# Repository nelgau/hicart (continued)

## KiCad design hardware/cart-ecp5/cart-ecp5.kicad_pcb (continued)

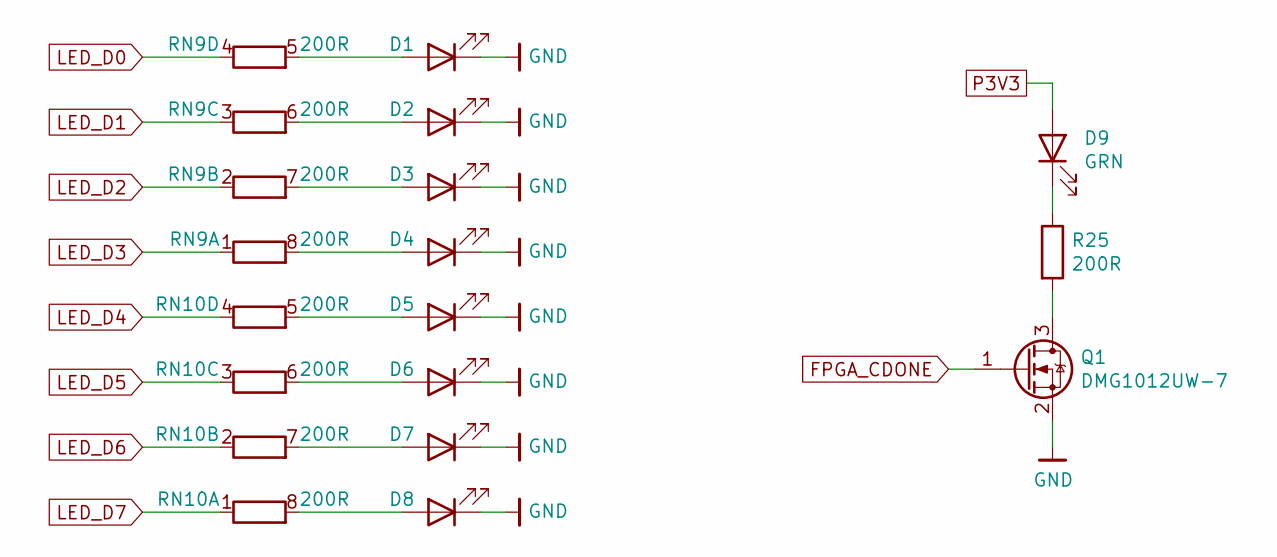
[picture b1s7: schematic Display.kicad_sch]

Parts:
D1, D2, D3, D4, D5, D6, D7, D8, D9: GRN; D_0603_1608Metric; MPN LTST-C191KGKT
Q1: DMG1012UW-7; SOT-323_SC-70; MPN DMG1012UW-7
R25: 200R; R_0402_1005Metric; MPN RC0402JR-07200RL
RN9, RN10: 200R; R_Array_Convex_4x0603; MPN YC164-JR-07200RL

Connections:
FPGA_CDONE: Q1.1 (G); also elsewhere on the board
GND: D1.1 (K), D2.1 (K), D3.1 (K), D4.1 (K), D5.1 (K), D6.1 (K), D7.1 (K), D8.1 (K), Q1.2 (S); also elsewhere on the board
LED_D0: RN9.4 (R4.1); also elsewhere on the board
LED_D1: RN9.3 (R3.1); also elsewhere on the board
LED_D2: RN9.2 (R2.1); also elsewhere on the board
LED_D3: RN9.1 (R1.1); also elsewhere on the board
LED_D4: RN10.4 (R4.1); also elsewhere on the board
LED_D5: RN10.3 (R3.1); also elsewhere on the board
LED_D6: RN10.2 (R2.1); also elsewhere on the board
LED_D7: RN10.1 (R1.1); also elsewhere on the board
unnamed: D1.2 (A), RN9.5 (R4.2)
unnamed: D2.2 (A), RN9.6 (R3.2)
unnamed: D3.2 (A), RN9.7 (R2.2)
unnamed: D4.2 (A), RN9.8 (R1.2)
unnamed: D5.2 (A), RN10.5 (R4.2)
unnamed: D6.2 (A), RN10.6 (R3.2)
unnamed: D7.2 (A), RN10.7 (R2.2)
unnamed: D8.2 (A), RN10.8 (R1.2)
unnamed: D9.1 (K), R25.1
unnamed: Q1.3 (D), R25.2
P3V3: D9.2 (A); also elsewhere on the board

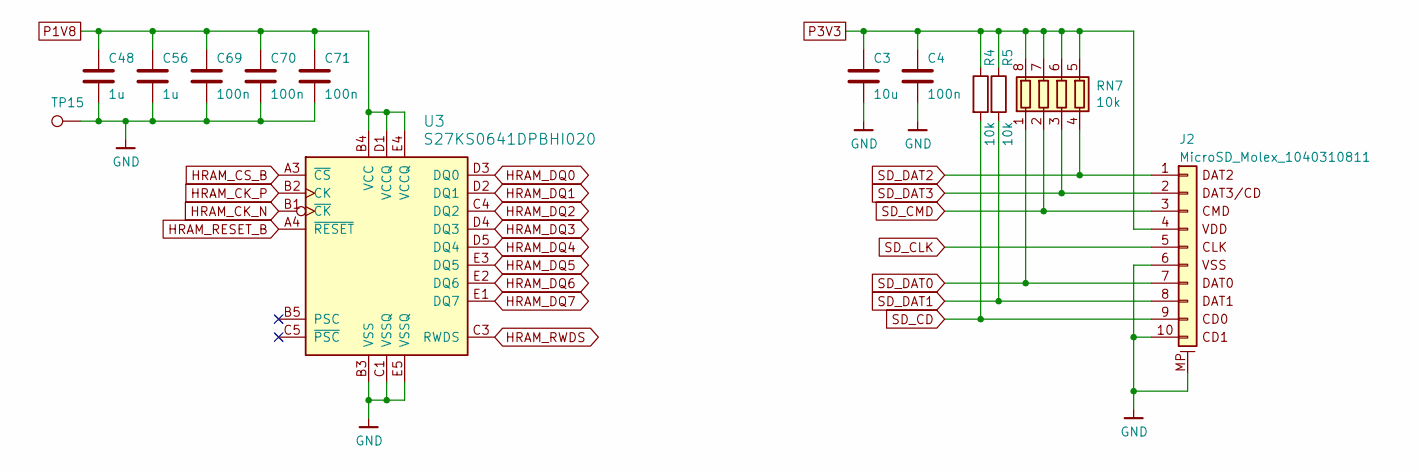
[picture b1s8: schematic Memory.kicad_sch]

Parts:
C3: 10u; C_0603_1608Metric; MPN CL10A106MQ8NNND
C4, C69, C70, C71: 100n; C_0402_1005Metric; MPN CL05B104KO5NNNC
C48, C56: 1u; C_0402_1005Metric; MPN CL05A105KO5NNNC
J2: MicroSD_Molex_1040310811; MPN 104031-0811
R4, R5: 10k; R_0402_1005Metric; MPN RC0402FR-0710KL
RN7: 10k; R_Array_Convex_4x0603; MPN YC164-FR-0710KL
TP15: TestPoint; TestPoint_Pad_D1.0mm
U3: S27KS0641DPBHI020; BGA-24_6.0x8.0mm_Layout5x5_P1.0mm_Pad0.4mm; MPN S27KS0641DPBHI020

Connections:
GND: C3.2, C4.2, C48.2, C56.2, C69.2, C70.2, C71.2, J2.6, J2.10 (DET), J2.MP (MountPin), TP15.1, U3.B3 (VSS), U3.C1 (VSSQ), U3.E5 (VSSQ); also elsewhere on the board
HRAM_CK_N: U3.B1 (~CK); also elsewhere on the board
HRAM_CK_P: U3.B2 (CK); also elsewhere on the board
HRAM_CS_B: U3.A3 (~CS); also elsewhere on the board
HRAM_DQ0: U3.D3 (DQ0); also elsewhere on the board
HRAM_DQ1: U3.D2 (DQ1); also elsewhere on the board
HRAM_DQ2: U3.C4 (DQ2); also elsewhere on the board
HRAM_DQ3: U3.D4 (DQ3); also elsewhere on the board
HRAM_DQ4: U3.D5 (DQ4); also elsewhere on the board
HRAM_DQ5: U3.E3 (DQ5); also elsewhere on the board
HRAM_DQ6: U3.E2 (DQ6); also elsewhere on the board
HRAM_DQ7: U3.E1 (DQ7); also elsewhere on the board
HRAM_RESET_B: U3.A4 (~RESET); also elsewhere on the board
HRAM_RWDS: U3.C3 (RWDS); also elsewhere on the board
P1V8: C48.1, C56.1, C69.1, C70.1, C71.1, U3.B4 (VCC), U3.D1 (VCCQ), U3.E4 (VCCQ); also elsewhere on the board
P3V3: C3.1, C4.1, J2.4, R4.1, R5.1, RN7.5 (R4.2), RN7.6 (R3.2), RN7.7 (R2.2), RN7.8 (R1.2); also elsewhere on the board
SD_CD: J2.9, R4.2; also elsewhere on the board
SD_CLK: J2.5; also elsewhere on the board
SD_CMD: J2.3, RN7.2 (R2.1); also elsewhere on the board
SD_DAT0: J2.7, RN7.1 (R1.1); also elsewhere on the board
SD_DAT1: J2.8, R5.2; also elsewhere on the board
SD_DAT2: J2.1, RN7.4 (R4.1); also elsewhere on the board
SD_DAT3: J2.2, RN7.3 (R3.1); also elsewhere on the board

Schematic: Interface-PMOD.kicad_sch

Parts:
J6: Conn_02x06_Odd_Even; PinSocket_2x06_P2.54mm_Horizontal

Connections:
GND: J6.3, J6.4; also elsewhere on the board
P3V3: J6.1, J6.2; also elsewhere on the board
PMOD_P1_D0: J6.11; also elsewhere on the board
PMOD_P1_D1: J6.9; also elsewhere on the board
PMOD_P1_D2: J6.7; also elsewhere on the board
PMOD_P1_D3: J6.5; also elsewhere on the board
PMOD_P1_D4: J6.12; also elsewhere on the board
PMOD_P1_D5: J6.10; also elsewhere on the board
PMOD_P1_D6: J6.8; also elsewhere on the board
PMOD_P1_D7: J6.6; also elsewhere on the board

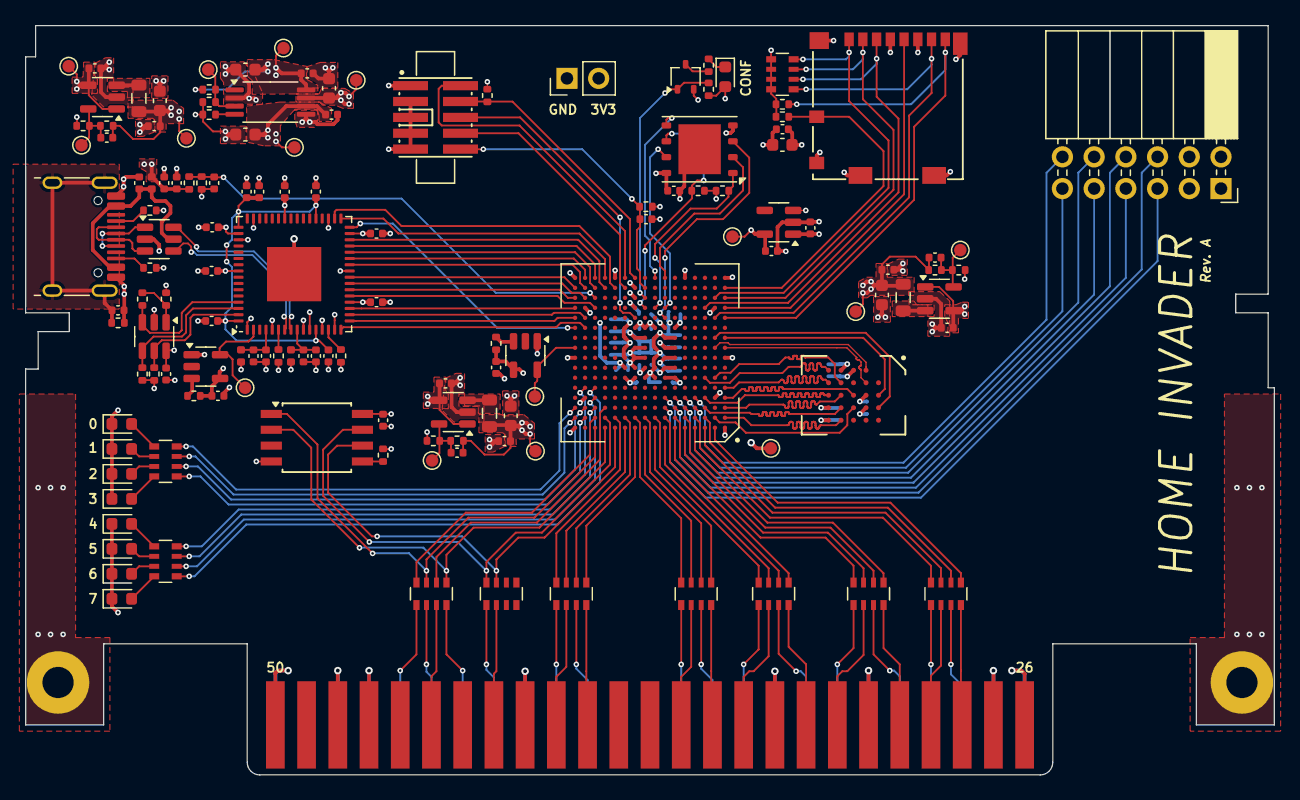
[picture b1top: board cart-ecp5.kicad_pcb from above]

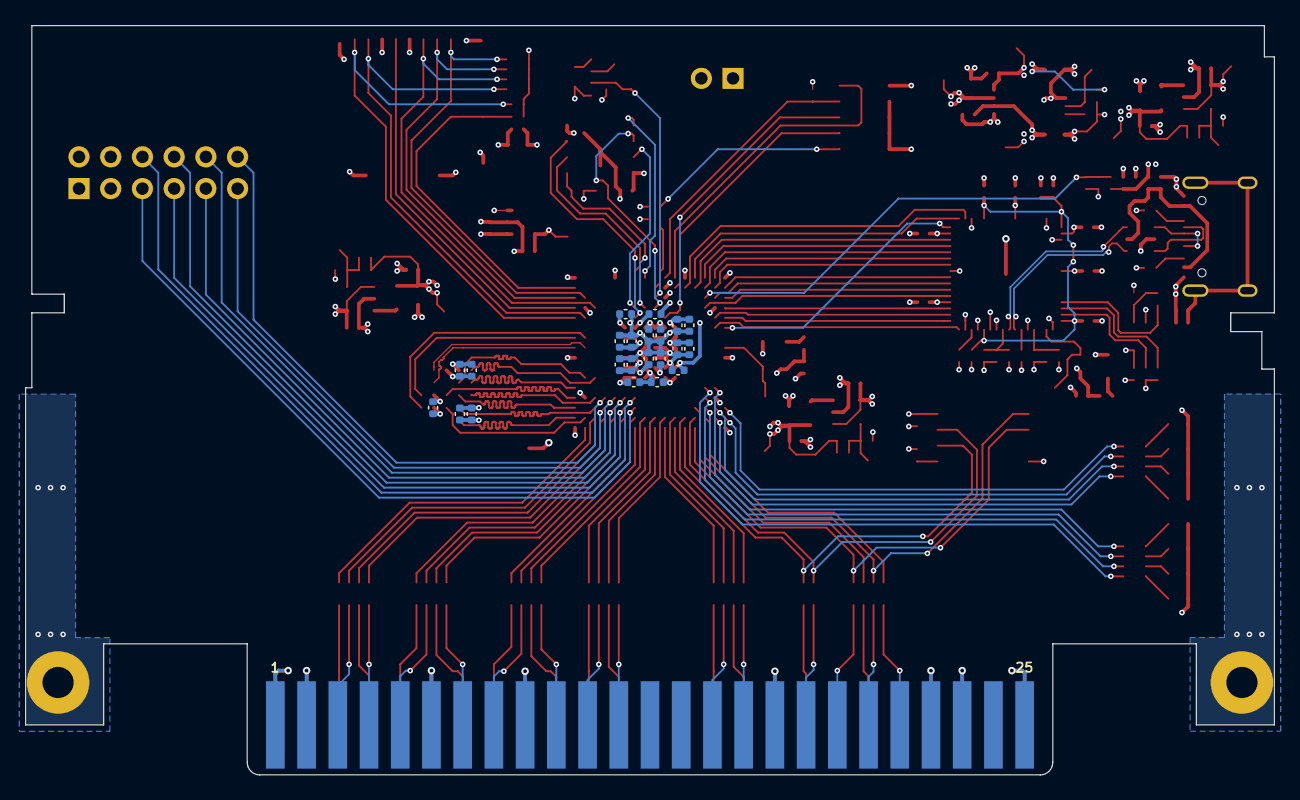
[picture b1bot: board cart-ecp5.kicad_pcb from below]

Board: 4 copper layers, 100.0 x 60.0 mm, 160 parts (22 on the bottom side), 165 nets.

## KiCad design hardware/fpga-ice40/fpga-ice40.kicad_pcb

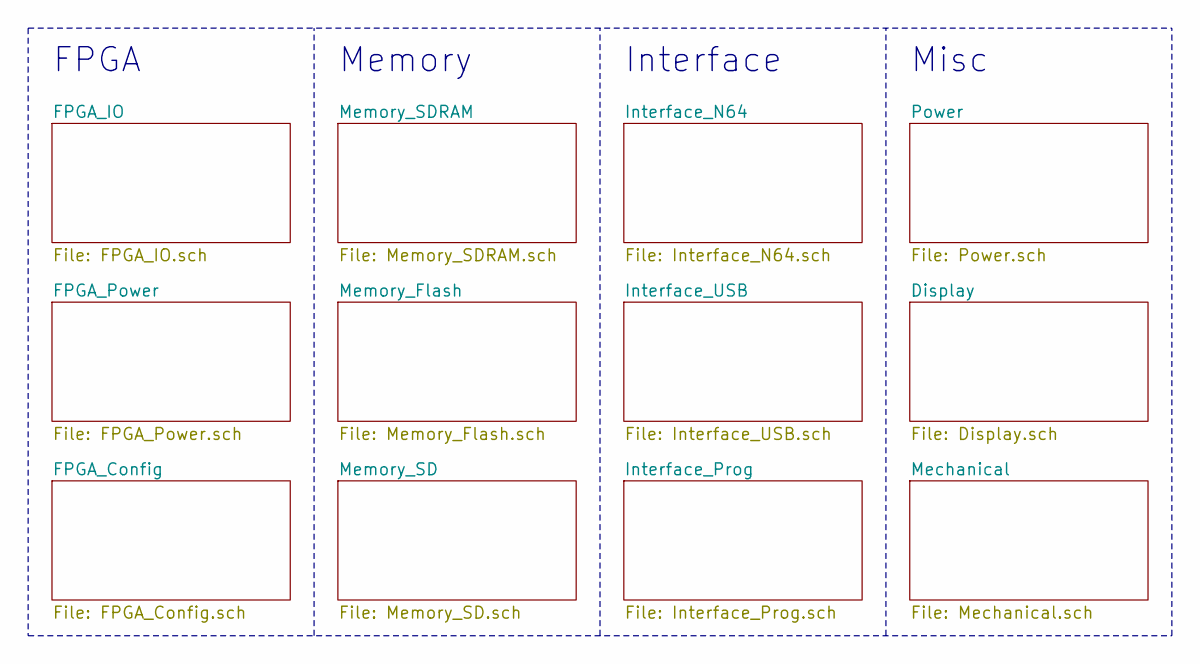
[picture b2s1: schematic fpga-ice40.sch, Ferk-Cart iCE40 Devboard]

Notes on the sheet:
Memory
Interface
Misc
FPGA

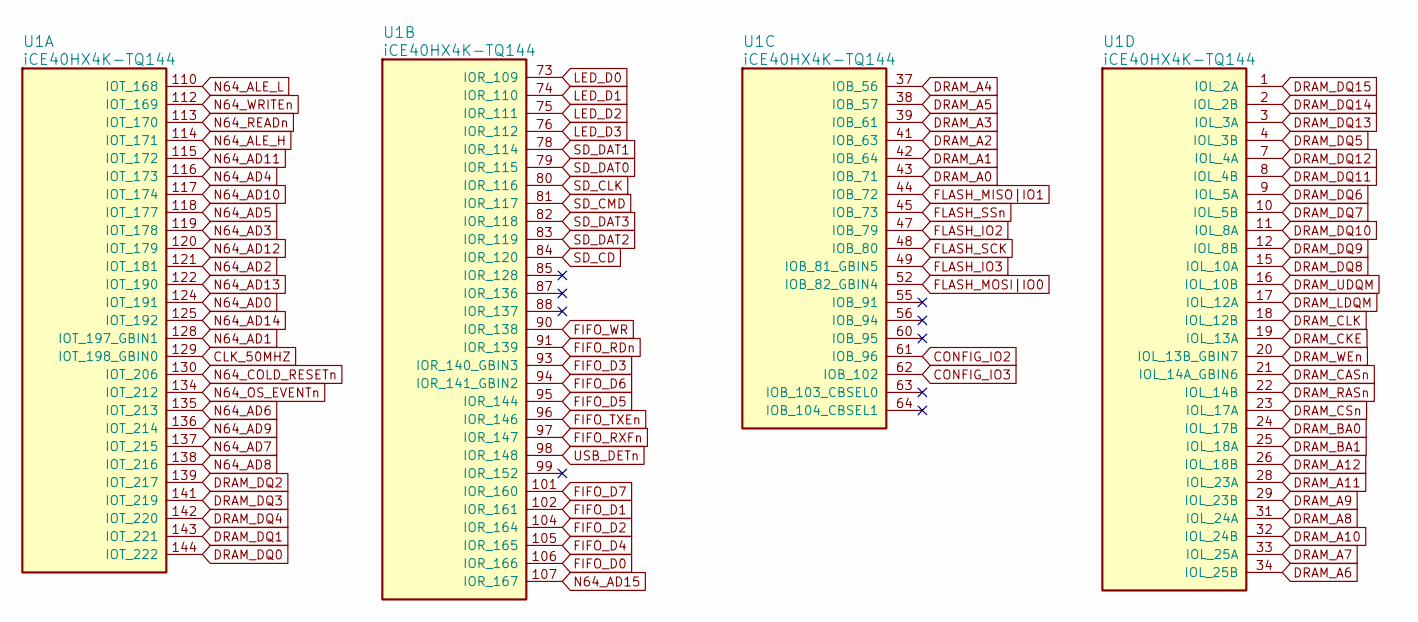
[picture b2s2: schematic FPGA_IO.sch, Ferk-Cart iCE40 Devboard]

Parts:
U1: iCE40HX4K-TQ144; TQFP-144_20x20mm_P0.5mm; MPN iCE40HX4K-TQ144

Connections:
CLK_50MHZ: U1.129 (IOT_198_GBIN0); also elsewhere on the board
CONFIG_IO2: U1.61 (IOB_96); also elsewhere on the board
CONFIG_IO3: U1.62 (IOB_102); also elsewhere on the board
DRAM_A0: U1.43 (IOB_71); also elsewhere on the board
DRAM_A1: U1.42 (IOB_64); also elsewhere on the board
DRAM_A2: U1.41 (IOB_63); also elsewhere on the board
DRAM_A3: U1.39 (IOB_61); also elsewhere on the board
DRAM_A4: U1.37 (IOB_56); also elsewhere on the board
DRAM_A5: U1.38 (IOB_57); also elsewhere on the board
DRAM_A6: U1.34 (IOL_25B); also elsewhere on the board
DRAM_A7: U1.33 (IOL_25A); also elsewhere on the board
DRAM_A8: U1.31 (IOL_24A); also elsewhere on the board
DRAM_A9: U1.29 (IOL_23B); also elsewhere on the board
DRAM_A10: U1.32 (IOL_24B); also elsewhere on the board
DRAM_A11: U1.28 (IOL_23A); also elsewhere on the board
DRAM_A12: U1.26 (IOL_18B); also elsewhere on the board
DRAM_BA0: U1.24 (IOL_17B); also elsewhere on the board
DRAM_BA1: U1.25 (IOL_18A); also elsewhere on the board
DRAM_CASn: U1.21 (IOL_14A_GBIN6); also elsewhere on the board
DRAM_CKE: U1.19 (IOL_13A); also elsewhere on the board
DRAM_CLK: U1.18 (IOL_12B); also elsewhere on the board
DRAM_CSn: U1.23 (IOL_17A); also elsewhere on the board
DRAM_DQ0: U1.144 (IOT_222); also elsewhere on the board
DRAM_DQ1: U1.143 (IOT_221); also elsewhere on the board
DRAM_DQ2: U1.139 (IOT_217); also elsewhere on the board
DRAM_DQ3: U1.141 (IOT_219); also elsewhere on the board
DRAM_DQ4: U1.142 (IOT_220); also elsewhere on the board
DRAM_DQ5: U1.4 (IOL_3B); also elsewhere on the board
DRAM_DQ6: U1.9 (IOL_5A); also elsewhere on the board
DRAM_DQ7: U1.10 (IOL_5B); also elsewhere on the board
DRAM_DQ8: U1.15 (IOL_10A); also elsewhere on the board
DRAM_DQ9: U1.12 (IOL_8B); also elsewhere on the board
DRAM_DQ10: U1.11 (IOL_8A); also elsewhere on the board
DRAM_DQ11: U1.8 (IOL_4B); also elsewhere on the board
DRAM_DQ12: U1.7 (IOL_4A); also elsewhere on the board
DRAM_DQ13: U1.3 (IOL_3A); also elsewhere on the board
DRAM_DQ14: U1.2 (IOL_2B); also elsewhere on the board
DRAM_DQ15: U1.1 (IOL_2A); also elsewhere on the board
DRAM_LDQM: U1.17 (IOL_12A); also elsewhere on the board
DRAM_RASn: U1.22 (IOL_14B); also elsewhere on the board
DRAM_UDQM: U1.16 (IOL_10B); also elsewhere on the board
DRAM_WEn: U1.20 (IOL_13B_GBIN7); also elsewhere on the board
FIFO_D0: U1.106 (IOR_166); also elsewhere on the board
FIFO_D1: U1.102 (IOR_161); also elsewhere on the board
FIFO_D2: U1.104 (IOR_164); also elsewhere on the board
FIFO_D3: U1.93 (IOR_140_GBIN3); also elsewhere on the board
FIFO_D4: U1.105 (IOR_165); also elsewhere on the board
FIFO_D5: U1.95 (IOR_144); also elsewhere on the board
FIFO_D6: U1.94 (IOR_141_GBIN2); also elsewhere on the board
FIFO_D7: U1.101 (IOR_160); also elsewhere on the board
FIFO_RDn: U1.91 (IOR_139); also elsewhere on the board
FIFO_RXFn: U1.97 (IOR_147); also elsewhere on the board
FIFO_TXEn: U1.96 (IOR_146); also elsewhere on the board
FIFO_WR: U1.90 (IOR_138); also elsewhere on the board
FLASH_IO2: U1.47 (IOB_79); also elsewhere on the board
FLASH_IO3: U1.49 (IOB_81_GBIN5); also elsewhere on the board
FLASH_MISO|IO1: U1.44 (IOB_72); also elsewhere on the board
FLASH_MOSI|IO0: U1.52 (IOB_82_GBIN4); also elsewhere on the board
FLASH_SCK: U1.48 (IOB_80); also elsewhere on the board
FLASH_SSn: U1.45 (IOB_73); also elsewhere on the board
LED_D0: U1.73 (IOR_109); also elsewhere on the board
LED_D1: U1.74 (IOR_110); also elsewhere on the board
LED_D2: U1.75 (IOR_111); also elsewhere on the board
LED_D3: U1.76 (IOR_112); also elsewhere on the board
N64_AD0: U1.124 (IOT_191); also elsewhere on the board
N64_AD1: U1.128 (IOT_197_GBIN1); also elsewhere on the board
N64_AD2: U1.121 (IOT_181); also elsewhere on the board
N64_AD3: U1.119 (IOT_178); also elsewhere on the board
N64_AD4: U1.116 (IOT_173); also elsewhere on the board
N64_AD5: U1.118 (IOT_177); also elsewhere on the board
N64_AD6: U1.135 (IOT_213); also elsewhere on the board
N64_AD7: U1.137 (IOT_215); also elsewhere on the board
N64_AD8: U1.138 (IOT_216); also elsewhere on the board
N64_AD9: U1.136 (IOT_214); also elsewhere on the board
N64_AD10: U1.117 (IOT_174); also elsewhere on the board
N64_AD11: U1.115 (IOT_172); also elsewhere on the board
N64_AD12: U1.120 (IOT_179); also elsewhere on the board
N64_AD13: U1.122 (IOT_190); also elsewhere on the board
N64_AD14: U1.125 (IOT_192); also elsewhere on the board
N64_AD15: U1.107 (IOR_167); also elsewhere on the board
N64_ALE_H: U1.114 (IOT_171); also elsewhere on the board
N64_ALE_L: U1.110 (IOT_168); also elsewhere on the board
N64_COLD_RESETn: U1.130 (IOT_206); also elsewhere on the board
N64_OS_EVENTn: U1.134 (IOT_212); also elsewhere on the board
N64_READn: U1.113 (IOT_170); also elsewhere on the board
N64_WRITEn: U1.112 (IOT_169); also elsewhere on the board
SD_CD: U1.84 (IOR_120); also elsewhere on the board
SD_CLK: U1.80 (IOR_116); also elsewhere on the board
SD_CMD: U1.81 (IOR_117); also elsewhere on the board
SD_DAT0: U1.79 (IOR_115); also elsewhere on the board
SD_DAT1: U1.78 (IOR_114); also elsewhere on the board
SD_DAT2: U1.83 (IOR_119); also elsewhere on the board
SD_DAT3: U1.82 (IOR_118); also elsewhere on the board
USB_DETn: U1.98 (IOR_148); also elsewhere on the board

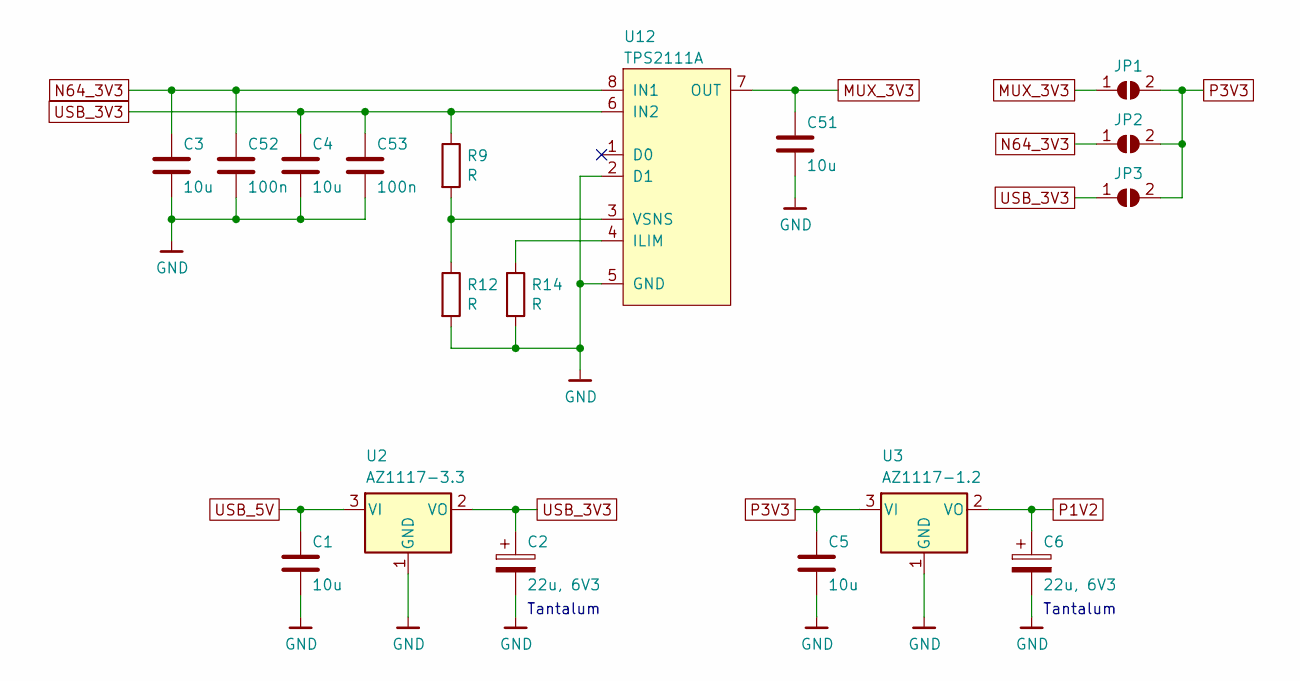
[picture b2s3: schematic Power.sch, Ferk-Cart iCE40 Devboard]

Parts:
C1, C5: 10u; C_0805_2012Metric; MPN CL21A106KAYNNNE
C2, C6: 22u, 6V3; CP_EIA-2012-15_AVX-P; MPN TAJP226M006RNJ
C3, C4, C51: 10u; C_0805_2012Metric
C52, C53: 100n; C_0603_1608Metric
JP1, JP2, JP3: SolderJumper_2_Open; SolderJumper-2_P1.3mm_Open_TrianglePad1.0x1.5mm
R9, R12, R14: R; R_0603_1608Metric
U2: AZ1117-3.3; SOT-223-3_TabPin2; MPN AZ1117H-3.3TRE1
U3: AZ1117-1.2; SOT-223-3_TabPin2; MPN AZ1117H-1.2TRE1
U12: TPS2111A; TSSOP-8_4.4x3mm_P0.65mm

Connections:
GND: C1.2, C2.2, C3.2, C4.2, C5.2, C6.2, C51.2, C52.2, C53.2, R12.2, R14.2, U2.1 (GND), U3.1 (GND), U12.2 (D1), U12.5 (GND); also elsewhere on the board
MUX_3V3: C51.1, JP1.1 (A), U12.7 (OUT)
N64_3V3: C3.1, C52.1, JP2.1 (A), U12.8 (IN1); also elsewhere on the board
unnamed: R9.2, R12.1, U12.3 (VSNS)
unnamed: R14.1, U12.4 (ILIM)
P1V2: C6.1, U3.2 (VO); also elsewhere on the board
P3V3: C5.1, JP1.2 (B), JP2.2 (B), JP3.2 (B), U3.3 (VI); also elsewhere on the board
USB_3V3: C2.1, C4.1, C53.1, JP3.1 (A), R9.1, U2.2 (VO), U12.6 (IN2)
USB_5V: C1.1, U2.3 (VI); also elsewhere on the board

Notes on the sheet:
Tantalum

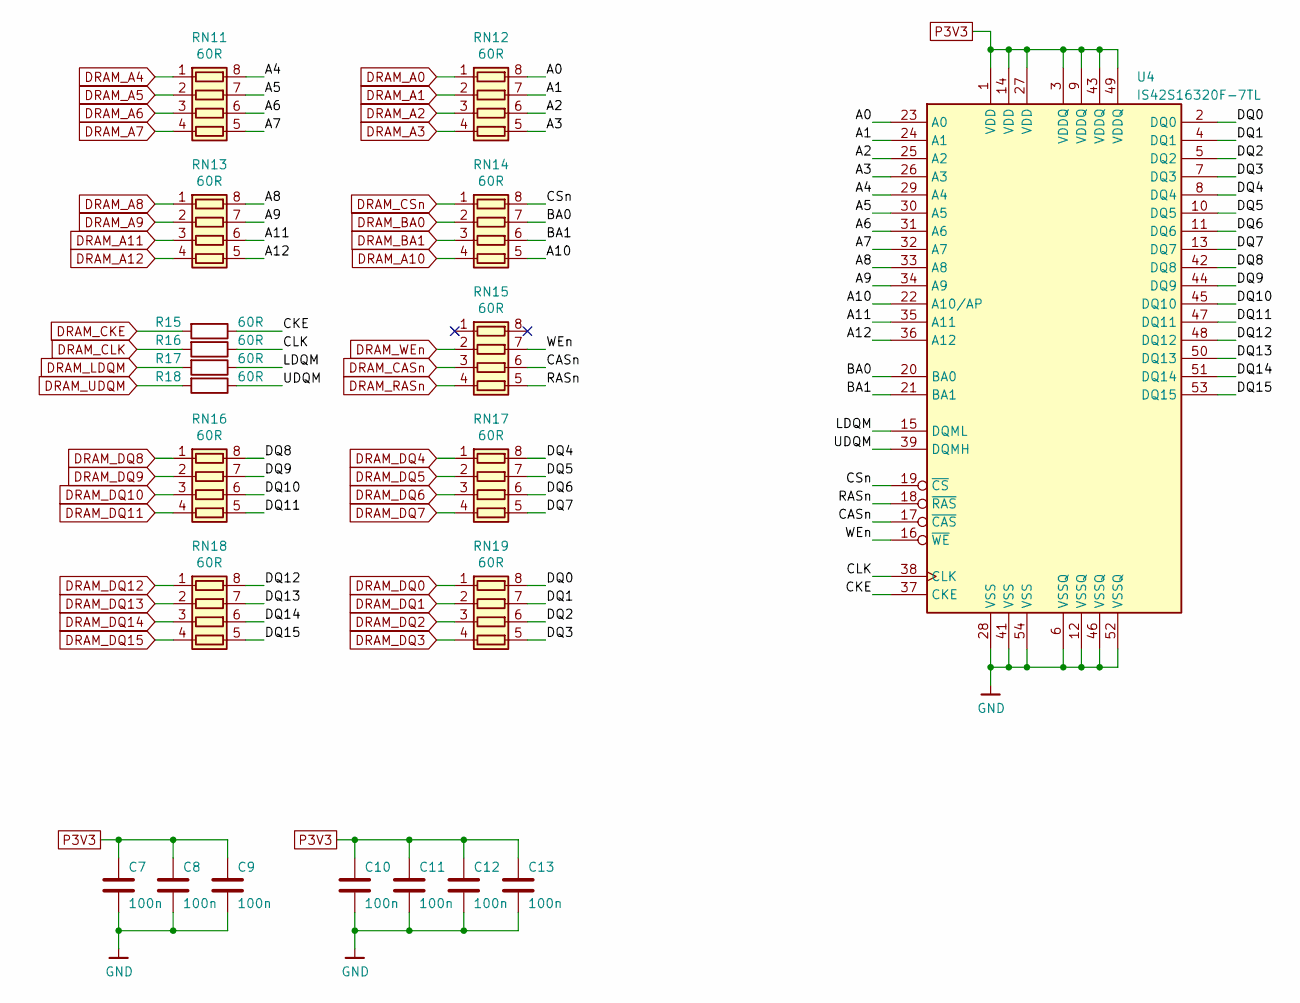
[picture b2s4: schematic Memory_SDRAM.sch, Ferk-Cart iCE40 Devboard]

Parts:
C7, C8, C9, C10, C11, C12, C13: 100n; C_0603_1608Metric; MPN CL10B104KB8NNNC
R15, R16, R17, R18: 60R; R_0603_1608Metric
RN11, RN12, RN13, RN14, RN15, RN16, RN17, RN18, RN19: 60R; R_Array_Convex_4x0603
U4: IS42S16320F-7TL; TSOP-II-54_22.2x10.16mm_P0.8mm; MPN IS42S16320F-7TL

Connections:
/Memory_SDRAM/A0: RN12.8 (R1.2), U4.23 (A0)
/Memory_SDRAM/A1: RN12.7 (R2.2), U4.24 (A1)
/Memory_SDRAM/A2: RN12.6 (R3.2), U4.25 (A2)
/Memory_SDRAM/A3: RN12.5 (R4.2), U4.26 (A3)
/Memory_SDRAM/A4: RN11.8 (R1.2), U4.29 (A4)
/Memory_SDRAM/A5: RN11.7 (R2.2), U4.30 (A5)
/Memory_SDRAM/A6: RN11.6 (R3.2), U4.31 (A6)
/Memory_SDRAM/A7: RN11.5 (R4.2), U4.32 (A7)
/Memory_SDRAM/A8: RN13.8 (R1.2), U4.33 (A8)
/Memory_SDRAM/A9: RN13.7 (R2.2), U4.34 (A9)
/Memory_SDRAM/A10: RN14.5 (R4.2), U4.22 (A10/AP)
/Memory_SDRAM/A11: RN13.6 (R3.2), U4.35 (A11)
/Memory_SDRAM/A12: RN13.5 (R4.2), U4.36 (A12)
/Memory_SDRAM/BA0: RN14.7 (R2.2), U4.20 (BA0)
/Memory_SDRAM/BA1: RN14.6 (R3.2), U4.21 (BA1)
/Memory_SDRAM/CASn: RN15.6 (R3.2), U4.17 (~CAS)
/Memory_SDRAM/CKE: R15.1, U4.37 (CKE)
/Memory_SDRAM/CLK: R16.1, U4.38 (CLK)
/Memory_SDRAM/CSn: RN14.8 (R1.2), U4.19 (~CS)
/Memory_SDRAM/DQ0: RN19.8 (R1.2), U4.2 (DQ0)
/Memory_SDRAM/DQ1: RN19.7 (R2.2), U4.4 (DQ1)
/Memory_SDRAM/DQ2: RN19.6 (R3.2), U4.5 (DQ2)
/Memory_SDRAM/DQ3: RN19.5 (R4.2), U4.7 (DQ3)
/Memory_SDRAM/DQ4: RN17.8 (R1.2), U4.8 (DQ4)
/Memory_SDRAM/DQ5: RN17.7 (R2.2), U4.10 (DQ5)
/Memory_SDRAM/DQ6: RN17.6 (R3.2), U4.11 (DQ6)
/Memory_SDRAM/DQ7: RN17.5 (R4.2), U4.13 (DQ7)
/Memory_SDRAM/DQ8: RN16.8 (R1.2), U4.42 (DQ8)
/Memory_SDRAM/DQ9: RN16.7 (R2.2), U4.44 (DQ9)
/Memory_SDRAM/DQ10: RN16.6 (R3.2), U4.45 (DQ10)
/Memory_SDRAM/DQ11: RN16.5 (R4.2), U4.47 (DQ11)
/Memory_SDRAM/DQ12: RN18.8 (R1.2), U4.48 (DQ12)
/Memory_SDRAM/DQ13: RN18.7 (R2.2), U4.50 (DQ13)
/Memory_SDRAM/DQ14: RN18.6 (R3.2), U4.51 (DQ14)
/Memory_SDRAM/DQ15: RN18.5 (R4.2), U4.53 (DQ15)
/Memory_SDRAM/LDQM: R17.1, U4.15 (DQML)
/Memory_SDRAM/RASn: RN15.5 (R4.2), U4.18 (~RAS)
/Memory_SDRAM/UDQM: R18.1, U4.39 (DQMH)
/Memory_SDRAM/WEn: RN15.7 (R2.2), U4.16 (~WE)
DRAM_A0: RN12.1 (R1.1); also elsewhere on the board
DRAM_A1: RN12.2 (R2.1); also elsewhere on the board
DRAM_A2: RN12.3 (R3.1); also elsewhere on the board
DRAM_A3: RN12.4 (R4.1); also elsewhere on the board
DRAM_A4: RN11.1 (R1.1); also elsewhere on the board
DRAM_A5: RN11.2 (R2.1); also elsewhere on the board
DRAM_A6: RN11.3 (R3.1); also elsewhere on the board
DRAM_A7: RN11.4 (R4.1); also elsewhere on the board
DRAM_A8: RN13.1 (R1.1); also elsewhere on the board
DRAM_A9: RN13.2 (R2.1); also elsewhere on the board
DRAM_A10: RN14.4 (R4.1); also elsewhere on the board
DRAM_A11: RN13.3 (R3.1); also elsewhere on the board
DRAM_A12: RN13.4 (R4.1); also elsewhere on the board
DRAM_BA0: RN14.2 (R2.1); also elsewhere on the board
DRAM_BA1: RN14.3 (R3.1); also elsewhere on the board
DRAM_CASn: RN15.3 (R3.1); also elsewhere on the board
DRAM_CKE: R15.2; also elsewhere on the board
DRAM_CLK: R16.2; also elsewhere on the board
DRAM_CSn: RN14.1 (R1.1); also elsewhere on the board
DRAM_DQ0: RN19.1 (R1.1); also elsewhere on the board
DRAM_DQ1: RN19.2 (R2.1); also elsewhere on the board
DRAM_DQ2: RN19.3 (R3.1); also elsewhere on the board
DRAM_DQ3: RN19.4 (R4.1); also elsewhere on the board
DRAM_DQ4: RN17.1 (R1.1); also elsewhere on the board
DRAM_DQ5: RN17.2 (R2.1); also elsewhere on the board
DRAM_DQ6: RN17.3 (R3.1); also elsewhere on the board
DRAM_DQ7: RN17.4 (R4.1); also elsewhere on the board
DRAM_DQ8: RN16.1 (R1.1); also elsewhere on the board
DRAM_DQ9: RN16.2 (R2.1); also elsewhere on the board
DRAM_DQ10: RN16.3 (R3.1); also elsewhere on the board
DRAM_DQ11: RN16.4 (R4.1); also elsewhere on the board
DRAM_DQ12: RN18.1 (R1.1); also elsewhere on the board
DRAM_DQ13: RN18.2 (R2.1); also elsewhere on the board
DRAM_DQ14: RN18.3 (R3.1); also elsewhere on the board
DRAM_DQ15: RN18.4 (R4.1); also elsewhere on the board
DRAM_LDQM: R17.2; also elsewhere on the board
DRAM_RASn: RN15.4 (R4.1); also elsewhere on the board
DRAM_UDQM: R18.2; also elsewhere on the board
DRAM_WEn: RN15.2 (R2.1); also elsewhere on the board
GND: C7.2, C8.2, C9.2, C10.2, C11.2, C12.2, C13.2, U4.6 (VSSQ), U4.12 (VSSQ), U4.28 (VSS), U4.41 (VSS), U4.46 (VSSQ), U4.52 (VSSQ), U4.54 (VSS); also elsewhere on the board
P3V3: C7.1, C8.1, C9.1, C10.1, C11.1, C12.1, C13.1, U4.1 (VDD), U4.3 (VDDQ), U4.9 (VDDQ), U4.14 (VDD), U4.27 (VDD), U4.43 (VDDQ), U4.49 (VDDQ); also elsewhere on the board

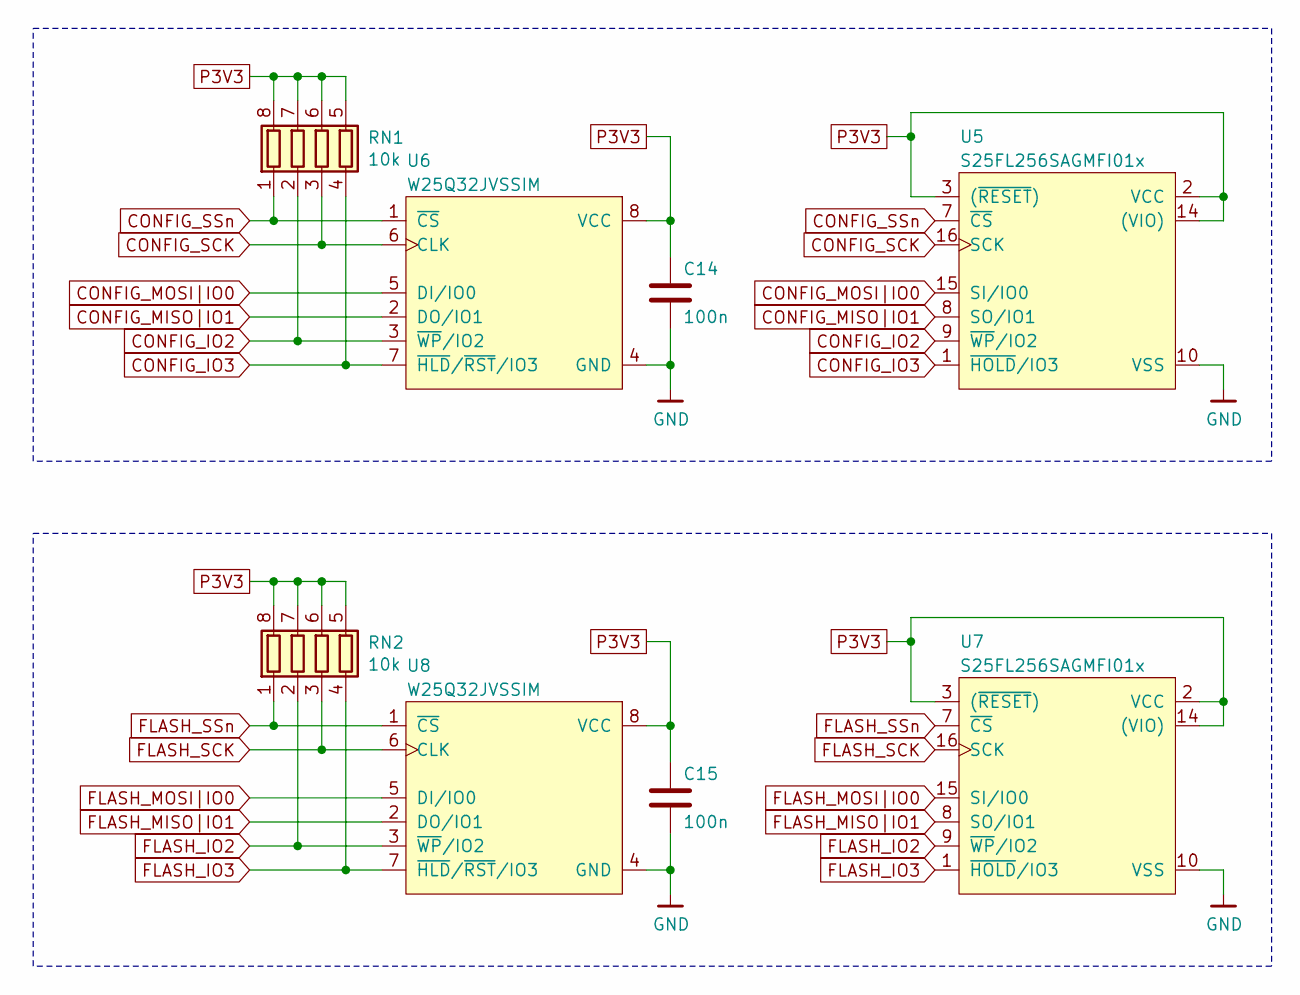
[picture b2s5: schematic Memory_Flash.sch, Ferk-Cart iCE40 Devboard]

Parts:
C14, C15: 100n; C_0603_1608Metric; MPN CL10B104KB8NNNC
RN1, RN2: 10k; R_Array_Convex_4x0603; MPN YC164-JR-0710KL
U5, U7: S25FL256SAGMFI01x; SOIC-16W_7.5x10.3mm_P1.27mm; MPN S25FL256SAGMFI013
U6, U8: W25Q32JVSSIM; SOIC-8_5.275x5.275mm_P1.27mm__No_CrtYd; MPN W25Q32JVSSIM (TR)

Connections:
CONFIG_IO2: RN1.2 (R2.1), U5.9 (~WP~/IO2), U6.3 (~WP~/IO2); also elsewhere on the board
CONFIG_IO3: RN1.4 (R4.1), U5.1 (~HOLD~/IO3), U6.7 (~HLD~/~RST~/IO3); also elsewhere on the board
CONFIG_MISO|IO1: U5.8 (SO/IO1), U6.2 (DO/IO1); also elsewhere on the board
CONFIG_MOSI|IO0: U5.15 (SI/IO0), U6.5 (DI/IO0); also elsewhere on the board
CONFIG_SCK: RN1.3 (R3.1), U5.16 (SCK), U6.6 (CLK); also elsewhere on the board
CONFIG_SSn: RN1.1 (R1.1), U5.7 (~CS), U6.1 (~CS); also elsewhere on the board
FLASH_IO2: RN2.2 (R2.1), U7.9 (~WP~/IO2), U8.3 (~WP~/IO2); also elsewhere on the board
FLASH_IO3: RN2.4 (R4.1), U7.1 (~HOLD~/IO3), U8.7 (~HLD~/~RST~/IO3); also elsewhere on the board
FLASH_MISO|IO1: U7.8 (SO/IO1), U8.2 (DO/IO1); also elsewhere on the board
FLASH_MOSI|IO0: U7.15 (SI/IO0), U8.5 (DI/IO0); also elsewhere on the board
FLASH_SCK: RN2.3 (R3.1), U7.16 (SCK), U8.6 (CLK); also elsewhere on the board
FLASH_SSn: RN2.1 (R1.1), U7.7 (~CS), U8.1 (~CS); also elsewhere on the board
GND: C14.2, C15.2, U5.10 (VSS), U6.4 (GND), U7.10 (VSS), U8.4 (GND); also elsewhere on the board
P3V3: C14.1, C15.1, RN1.5 (R4.2), RN1.6 (R3.2), RN1.7 (R2.2), RN1.8 (R1.2), RN2.5 (R4.2), RN2.6 (R3.2), RN2.7 (R2.2), RN2.8 (R1.2), U5.2 (VCC), U5.3 ((~RESET~)), U5.14 ((VIO)), U6.8 (VCC), U7.2 (VCC), U7.3 ((~RESET~)), U7.14 ((VIO)), U8.8 (VCC); also elsewhere on the board

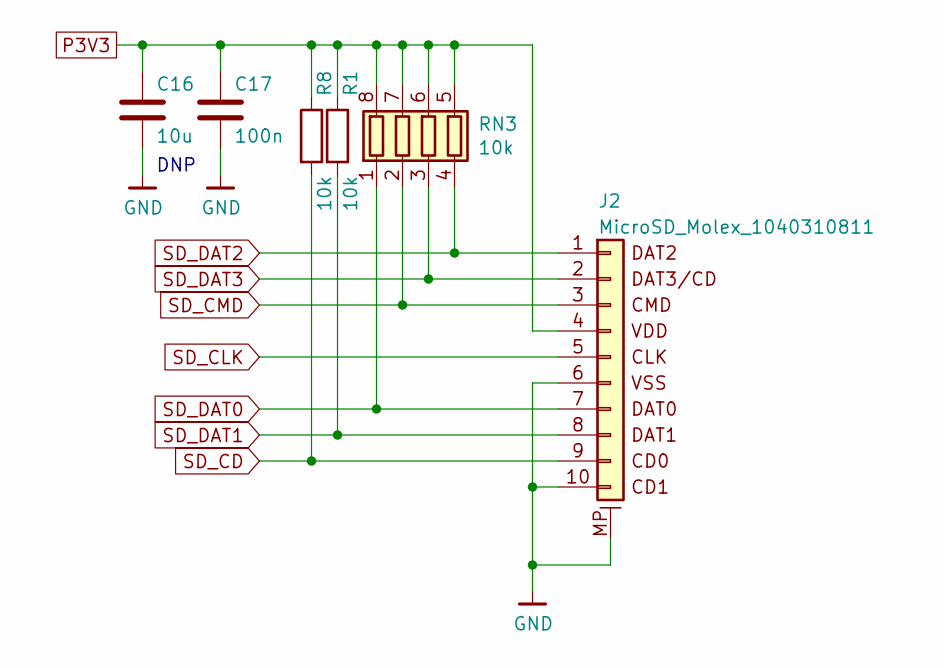
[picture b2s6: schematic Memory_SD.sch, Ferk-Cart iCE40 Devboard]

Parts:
C16: 10u; C_0805_2012Metric; MPN CL21A106KAYNNNE
C17: 100n; C_0603_1608Metric; MPN CL10B104KB8NNNC
J2: MicroSD_Molex_1040310811; MPN 104031-0811
R1, R8: 10k; R_0603_1608Metric; MPN RC0603FR-0710KL
RN3: 10k; R_Array_Convex_4x0603; MPN YC164-JR-0710KL

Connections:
GND: C16.2, C17.2, J2.6, J2.10 (DET), J2.MP (MountPin); also elsewhere on the board
P3V3: C16.1, C17.1, J2.4, R1.1, R8.1, RN3.5 (R4.2), RN3.6 (R3.2), RN3.7 (R2.2), RN3.8 (R1.2); also elsewhere on the board
SD_CD: J2.9, R8.2; also elsewhere on the board
SD_CLK: J2.5; also elsewhere on the board
SD_CMD: J2.3, RN3.2 (R2.1); also elsewhere on the board
SD_DAT0: J2.7, RN3.1 (R1.1); also elsewhere on the board
SD_DAT1: J2.8, R1.2; also elsewhere on the board
SD_DAT2: J2.1, RN3.4 (R4.1); also elsewhere on the board
SD_DAT3: J2.2, RN3.3 (R3.1); also elsewhere on the board

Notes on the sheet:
DNP

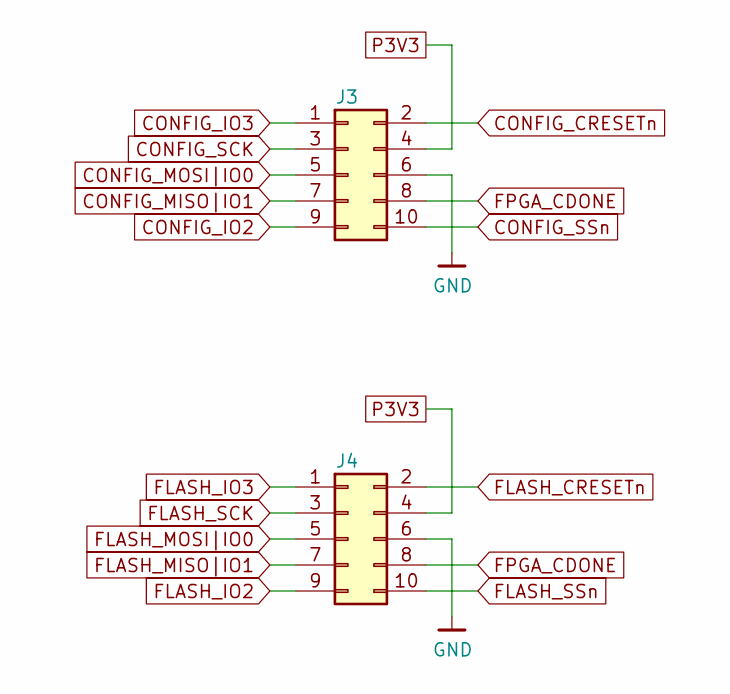
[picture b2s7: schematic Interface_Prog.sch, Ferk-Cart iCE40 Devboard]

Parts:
J3, J4: FTSH-105-01-L-DV-K; Samtec_FTSH-105-XX-X-DV-Mating; MPN FTSH-105-01-L-DV-K

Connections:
CONFIG_CRESETn: J3.2; also elsewhere on the board
CONFIG_IO2: J3.9; also elsewhere on the board
CONFIG_IO3: J3.1; also elsewhere on the board
CONFIG_MISO|IO1: J3.7; also elsewhere on the board
CONFIG_MOSI|IO0: J3.5; also elsewhere on the board
CONFIG_SCK: J3.3; also elsewhere on the board
CONFIG_SSn: J3.10; also elsewhere on the board
FLASH_CRESETn: J4.2; also elsewhere on the board
FLASH_IO2: J4.9; also elsewhere on the board
FLASH_IO3: J4.1; also elsewhere on the board
FLASH_MISO|IO1: J4.7; also elsewhere on the board
FLASH_MOSI|IO0: J4.5; also elsewhere on the board
FLASH_SCK: J4.3; also elsewhere on the board
FLASH_SSn: J4.10; also elsewhere on the board
FPGA_CDONE: J3.8, J4.8; also elsewhere on the board
GND: J3.6, J4.6; also elsewhere on the board
P3V3: J3.4, J4.4; also elsewhere on the board
